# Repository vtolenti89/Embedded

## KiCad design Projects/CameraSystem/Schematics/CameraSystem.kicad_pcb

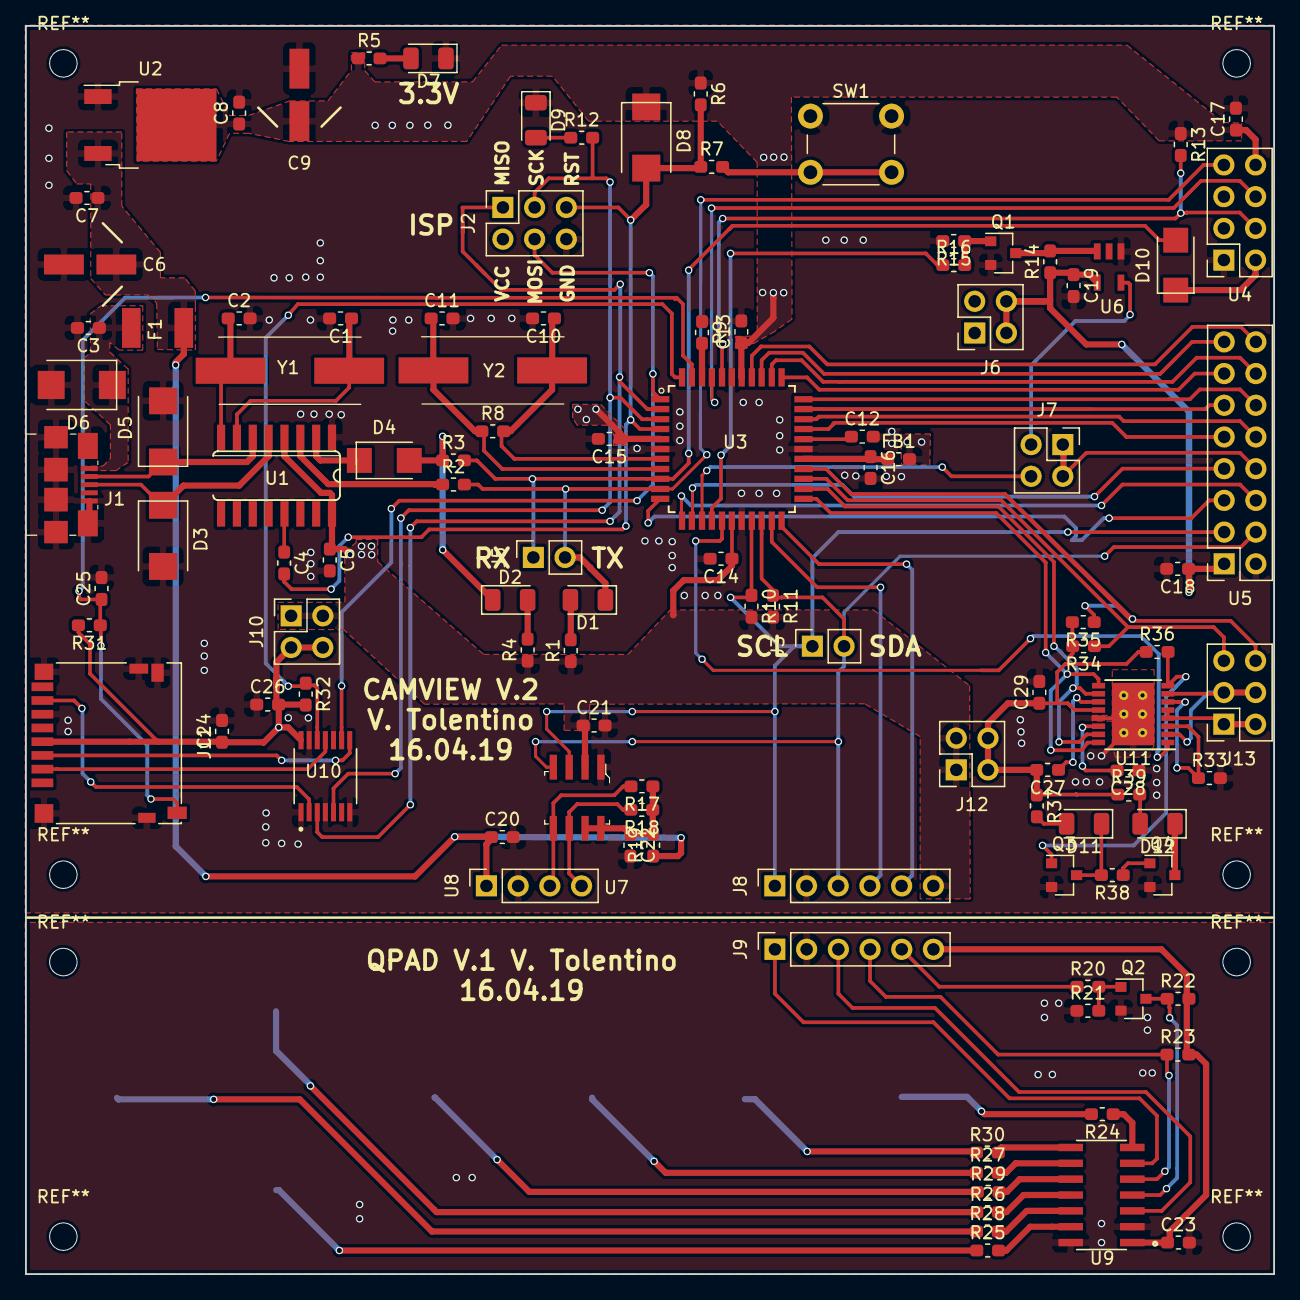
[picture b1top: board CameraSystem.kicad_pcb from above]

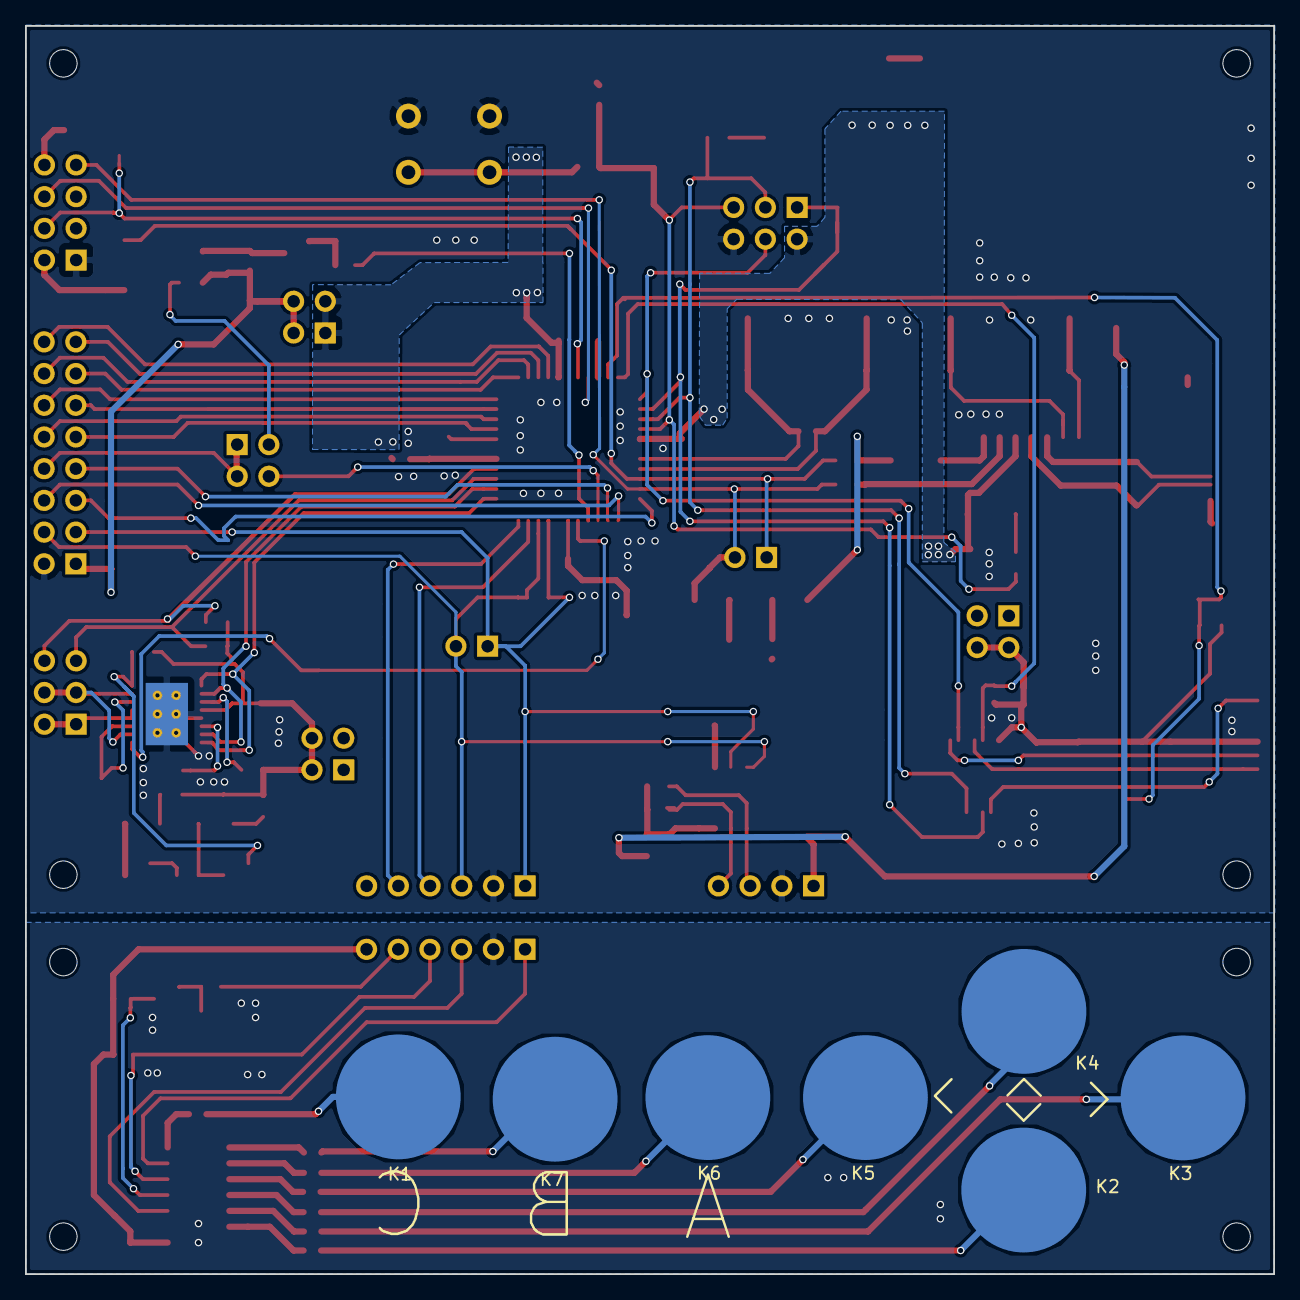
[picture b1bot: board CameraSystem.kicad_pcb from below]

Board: 2 copper layers, 100.0 x 100.0 mm, 119 parts (7 on the bottom side), 101 nets.

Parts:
C1, C2, C10, C11: 27p; C_0603_1608Metric_Pad1.05x0.95mm_HandSolder
C3, C4, C5, C12, C13, C14, C15, C16, C17, C18, C19, C20, C21, C22, C23, C24, C25, C26: 100n; C_0603_1608Metric_Pad1.05x0.95mm_HandSolder
C6, C9: EEE1VA470WP; PANASONIC_AL_SMD_D_D8
C7, C8: 1u; C_0603_1608Metric_Pad1.05x0.95mm_HandSolder
C27: 10n; C_0603_1608Metric_Pad1.05x0.95mm_HandSolder
C28: 2u2; C_0603_1608Metric_Pad1.05x0.95mm_HandSolder
C29: 10u; C_0603_1608Metric_Pad1.05x0.95mm_HandSolder
D1: BLUE_LED; LED_1206_3216Metric
D2: YELLOW_LED; LED_1206_3216Metric
D3, D5, D6, D8: SMBJ5.0CA; SMB_DO-214AA
D4, D10: SS14; SMA_DO-214AC
D7, D11: GREEN_LED; LED_1206_3216Metric
D9: LED; LED_1206_3216Metric
D12: RED_LED; LED_1206_3216Metric
F1: MF-MSMF075/24; PTC_MF-MSMF
FB1: BLM18PG121SN1D; R_0603_1608Metric_Pad1.05x0.95mm_HandSolder
J1: 10118192-0001LF; USB_Micro_B_Female_10118192
J2, J13: Conn_02x03_Odd_Even; PinSocket_2x03_P2.54mm_Vertical
J3, J5: Conn_01x02; PinSocket_1x02_P2.54mm_Vertical
J6, J7, J10, J12: Conn_02x02_Odd_Even; PinSocket_2x02_P2.54mm_Vertical
J8, J9: Conn_01x06; PinSocket_1x06_P2.54mm_Vertical
J11: DM3D-SF; microSD_HC_Hirose_DM3D-SF
K1, K2, K3, K4, K5, K6, K7: TouchPad; QPad_Round_D10
Q1, Q2, Q3, Q4: BC847; SOT-23
R1, R4, R5, R12, R37, R39: 560; R_0603_1608Metric_Pad1.05x0.95mm_HandSolder
R2, R3: 1k; R_0603_1608Metric_Pad1.05x0.95mm_HandSolder
R6, R9, R13, R14, R15, R31, R32, R34, R35: 10k; R_0603_1608Metric_Pad1.05x0.95mm_HandSolder
R7: 330; R_0603_1608Metric_Pad1.05x0.95mm_HandSolder
R8: 1M; R_0603_1608Metric_Pad1.05x0.95mm_HandSolder
R10, R11: 2K2; R_0603_1608Metric_Pad1.05x0.95mm_HandSolder
R16: 4k7; R_0603_1608Metric_Pad1.05x0.95mm_HandSolder
R17, R18: 1K74; R_0603_1608Metric_Pad1.05x0.95mm_HandSolder
R19: 200k; R_0603_1608Metric_Pad1.05x0.95mm_HandSolder
R20, R24, R25, R26, R27, R28, R29, R30: 4K7; R_0603_1608Metric_Pad1.05x0.95mm_HandSolder
R21, R22, R23: 10K; R_0603_1608Metric_Pad1.05x0.95mm_HandSolder
R33: 1; R_0603_1608Metric_Pad1.05x0.95mm_HandSolder
R36, R38: 47k; R_0603_1608Metric_Pad1.05x0.95mm_HandSolder
SW1: SW_Push; SW_PUSH_6mm_H4.3mm
U1: CH340; SO16
U2: AZ1117CD-3.3TRG1DICT-ND; TO-252-2
U3: ATMEGA16A-AU; QFP80P1200X1200X120-44N
U4: ESP8266; PinSocket_2x04_P2.54mm_Vertical
U5: OV7670; PinSocket_2x08_P2.54mm_Vertical
U6: SIT2001BI-S2-33E-24.000000G; SiT2001B_SOT23
U7: PCA9306D_118; SOIC-8_W3.9mm
U8: LCD_2x16_w_i2c; PinSocket_1x04_P2.54mm_Vertical
U9: AT42QT1070-SSUR
U10: MC74HC125ADTR2G; MC74HC125A_TSSOP−14
U11: DRV8833PWP; HTSSOP-16-1EP_4.4x5mm_P0.65mm_EP3.4x5mm_Mask2.46x2.31mm_The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
Y1: ABLS-12.000MHZ-B2-T; ABLS2-10.000MHZ-D4Y-T
Y2: ABLS2-10.000MHZ-D4Y-T

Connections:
/Camera/CAM_CLK: J7.4, U3.14
/Camera/CAM_D0: U3.37, U5.16
/Camera/CAM_D1: U3.36, U5.15
/Camera/CAM_D2: U3.35, U5.14
/Camera/CAM_D3: U3.34, U5.13
/Camera/CAM_D4: U3.33, U5.12
/Camera/CAM_D5: U3.32, U5.11
/Camera/CAM_D6: U3.31, U5.10
/Camera/CAM_D7: U3.30, U5.9
/Camera/CAM_HSYNC: U3.12, U5.6
/Camera/CAM_PCLK: U3.13, U5.7
/Camera/CAM_VSYNC: U3.11, U5.5
/Camera/CAM_XCLK_CTL: R16.1, U3.15
/Camera/SCL_3V3: J3.1, J8.1, R10.1, U3.19, U5.3, U7.3
/Camera/SDA_3V3: J3.2, J8.3, R11.1, U3.20, U5.4, U7.4
/Camera/VDD_3V3: C5.1, C8.1, C9.1, C13.1, C14.1, C15.1, C17.1, C21.1, D8.1, FB1.2, J2.2, J6.1, J6.3, J8.6, J10.1, J10.3, J12.1, J12.3, R1.1, R4.1, R5.1, R6.1, R10.2, R11.2, R13.1, U1.4, U1.16, U2.2, U3.5, U3.17, U3.38, U4.8, U7.2
/Camera/VDD_3V3_IN: C18.1, C19.1, J6.2, J6.4, R14.1, U5.1, U6.4
/Display/SCL_5V0: R18.2, U7.6, U8.4
/Display/SDA_5V0: R17.2, U7.5, U8.3
/Display/VDD_5V0: C6.1, C7.1, C20.1, F1.1, R19.1, U2.3, U8.1
/Input_Interface/USB_DN: D5.1, J1.2, U1.6
/Input_Interface/USB_DP: D3.1, J1.3, U1.5
/Input_Interface/USB_VCC: C3.1, D6.1, F1.2, J1.1
/Keypad/QP_GND: C23.2, J9.2, Q2.2, R21.1, U9.2, U9.14
/Keypad/QT_CHN: J9.4, R23.1, U9.5
/Keypad/QT_RST: J9.5, R20.1
/Keypad/SCL_3V3: J9.1, U9.6
/Keypad/SDA_3V3: J9.3, U9.3
/Keypad/VDD_3V3: C23.1, J9.6, R22.2, R23.2, U9.1
/Keypad/_QT_RST_IN: Q2.3, R22.1, U9.4
/Memory/SD_CS_IN: J11.2, U10.11
/Memory/SD_DATA_IN: J11.3, U10.8
/Memory/SD_DATA_OUT: J11.7, U10.2
/Memory/VDD_3V3_IN: C24.1, C26.2, J10.2, J10.4, J11.4, R31.2, R32.2, U10.14
/Memory/_SD_DET: C25.1, J11.10, R31.1, U3.43
/Microcontroller/CS: R32.1, U3.44, U10.12
/Microcontroller/MISO: J2.1, U3.2, U10.3
/Microcontroller/MOSI: J2.4, U3.1, U10.9
/Microcontroller/M_NSLEEP: U3.16, U11.1
/Microcontroller/M_PWM_IN_1: U3.23, U11.9, U11.16
/Microcontroller/M_PWM_IN_2: U3.24, U11.10, U11.15
/Microcontroller/QT_CHN: J8.4, U3.21
/Microcontroller/QT_RST: J8.5, U3.22
/Microcontroller/SCK: J2.3, R12.2, U3.3, U10.5
/Microcontroller/SENSOR1: J13.5, R34.1, U3.25
/Microcontroller/SENSOR2: J13.6, R35.1, U3.26
/Microcontroller/U2_SPI_RST: C4.2, D8.2, J2.5, R6.2, R7.1, U3.4
/Microcontroller/UC_SPI_RX: D10.2, J5.1, R3.2, U3.9
/Microcontroller/UC_SPI_TX: D1.1, J5.2, R2.2, U3.10, U4.7
/Microcontroller/WIFI_EN: R13.2, U3.40, U4.4
/Microcontroller/WIFI_RST: U3.41, U4.6
/Motor/M_PWM_OUT_1: J13.3, J13.4, U11.2, U11.7
/Motor/M_PWM_OUT_2: J13.1, J13.2, U11.4, U11.5
/Motor/VDD_3V3_CON_IN: C27.2, C29.1, J12.2, J12.4, R34.2, R35.2, R36.1, R37.1, R39.1, U11.12
GND: C1.2, C2.2, C3.2, C5.2, C6.2, C7.2, C8.2, C9.2, C10.2, C11.2, C12.2, C13.2, C14.2, C15.2, C16.2, C17.2, C18.2, C19.2, C20.2, C21.2, C22.2, C24.2, C25.2, C26.1, C28.1, C29.2, D3.2, D5.2, D6.2, D7.1, D9.1, J1.5, J1.SH, J2.6, J8.2, J11.6, J11.9, J11.11, Q1.2, Q3.2, Q4.2, R9.1, R15.2, R33.2, SW1.1, U1.1, U2.1, U3.6, U3.18, U3.28, U3.39, U4.1, U5.2, U6.1, U7.1, U8.2, U10.1, U10.4, U10.7, U10.10, U10.13, U11.13, U11.17
unnamed: C1.1, U1.7, Y1.1
unnamed: C2.1, U1.8, Y1.2
unnamed: C4.1, U1.13
unnamed: C10.1, R8.2, U3.7, Y2.1
unnamed: C11.1, R8.1, U3.8, Y2.2
unnamed: C12.1, U3.29
unnamed: C16.1, FB1.1, U3.27
unnamed: C22.1, R17.1, R18.1, R19.2, U7.7, U7.8
unnamed: C27.1, U11.11
unnamed: C28.2, U11.14
unnamed: D1.2, R1.2
unnamed: D2.1, D4.2, R3.1
unnamed: D2.2, R4.2
unnamed: D4.1, U1.2
unnamed: D7.2, R5.2
unnamed: D9.2, R12.1
unnamed: D10.1, U4.2
unnamed: D11.1, Q3.3, R38.2
unnamed: D11.2, R37.2
unnamed: D12.1, Q4.3
unnamed: D12.2, R39.2
unnamed: J7.1, J7.3, U5.8
unnamed: J7.2, U6.5
unnamed: K1.1, R24.2
unnamed: K2.1, R25.1
unnamed: K3.1, R28.1
unnamed: K4.1, R26.1
unnamed: K5.1, R29.1
unnamed: K6.1, R27.1
unnamed: K7.1, R30.1
unnamed: Q1.1, R15.1, R16.2
unnamed: Q1.3, R14.2, U6.3
unnamed: Q2.1, R20.2, R21.2
unnamed: Q3.1, R36.2, U11.8
unnamed: Q4.1, R38.1
unnamed: R2.1, U1.3
unnamed: R7.2, SW1.2
unnamed: R9.2, U3.42
unnamed: R24.1, U9.7
unnamed: R25.2, U9.13
unnamed: R26.2, U9.11
unnamed: R27.2, U9.9
unnamed: R28.2, U9.12
unnamed: R29.2, U9.10
unnamed: R30.2, U9.8
unnamed: R33.1, U11.3, U11.6

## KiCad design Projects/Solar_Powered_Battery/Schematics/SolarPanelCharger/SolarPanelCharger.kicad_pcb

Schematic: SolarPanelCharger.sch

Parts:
C1, C2: 100n; C_0603_1608Metric_Pad1.05x0.95mm_HandSolder
D1, D2: SS14; SMA_DO-214AC
Q1, Q2: BC847; SOT-23
R1, R2: 51k; R_0603_1608Metric_Pad1.05x0.95mm_HandSolder
R3: 18k; R_0603_1608Metric_Pad1.05x0.95mm_HandSolder
R4, R9: 100k; R_0603_1608Metric_Pad1.05x0.95mm_HandSolder
R5, R8, R10: 10k; R_0603_1608Metric_Pad1.05x0.95mm_HandSolder
R6: 100; R_0603_1608Metric_Pad1.05x0.95mm_HandSolder
R7: 47k; R_0603_1608Metric_Pad1.05x0.95mm_HandSolder
U1: LM358; SOP-8_3.76x4.96mm_P1.27mm
U2: TL431DBZ; SOT-23

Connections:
/BOOST_5V0/BOOST_IN: D2.2; also elsewhere on the board
/Buck_5V0/BUCK_IN: D1.2, R1.1; also elsewhere on the board
/EN_BAT: Q2.3 (C), R10.2; also elsewhere on the board
/LOGIC_SUPPLY: C1.1, C2.1, D1.1, D2.1, R5.1, R8.1, R10.1, U1.8 (V+)
/VREF_3V0: R3.1, R5.2, U1.3 (+), U2.1
/_EN_BAT: Q1.3 (C), R8.2, R9.1; also elsewhere on the board
GND: C1.2, C2.2, Q1.2 (E), Q2.2 (E), R2.2, R4.2, R7.2, U1.4 (V-), U1.5 (+), U2.3; also elsewhere on the board
unnamed: Q1.1 (B), R6.1, R7.1
unnamed: Q2.1 (B), R9.2
unnamed: R1.2, R2.1, U1.2 (-)
unnamed: R3.2, R4.1, U2.2
unnamed: R6.2, U1.1
unnamed: U1.6 (-), U1.7

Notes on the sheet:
Solar Panel
Switch to battery if the input voltage is below 6V

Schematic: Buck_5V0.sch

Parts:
C3: 100u; CP_Radial_D5.0mm_P2.50mm
C4: 22u; C_0603_1608Metric_Pad1.05x0.95mm_HandSolder
C5: 6n8; C_0603_1608Metric_Pad1.05x0.95mm_HandSolder
D5: SS24; SMB_DO-214AA
L1: 15u; CD54
R11, R12: 3k3; R_0603_1608Metric_Pad1.05x0.95mm_HandSolder
R13: 5k1; R_0603_1608Metric_Pad1.05x0.95mm_HandSolder
R14: 10k; R_0603_1608Metric_Pad1.05x0.95mm_HandSolder
R15: 33k; R_0603_1608Metric_Pad1.05x0.95mm_HandSolder
U3: TD1583; SOP-8_3.76x4.96mm_P1.27mm

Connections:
/Buck_5V0/BUCK_5V0: C4.2, C5.2, L1.1, R13.1; also elsewhere on the board
/Buck_5V0/BUCK_IN: C3.1, R14.2, U3.2; also elsewhere on the board
/Buck_5V0/EN: R14.1, R15.1, U3.7
GND: C3.2, C4.1, D5.2, R11.2, R12.2, R15.2, U3.4; also elsewhere on the board
unnamed: C5.1, R11.1, R12.1, R13.2, U3.5
unnamed: D5.1, L1.2, U3.3

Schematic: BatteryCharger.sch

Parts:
C6, C7: 10u; C_0603_1608Metric_Pad1.05x0.95mm_HandSolder
D6: YELLOW; LED_1206_3216Metric_Pad1.42x1.75mm_HandSolder
D7: GREEN; LED_1206_3216Metric_Pad1.42x1.75mm_HandSolder
J2: Conn_01x05_Female; PinSocket_1x05_P2.54mm_Vertical
Q3: BC847; SOT-23
R16, R17: 1; R_0603_1608Metric_Pad1.05x0.95mm_HandSolder
R18: 33k; R_0603_1608Metric_Pad1.05x0.95mm_HandSolder
R19, R23: 10k; R_0603_1608Metric_Pad1.05x0.95mm_HandSolder
R20: 18k; R_0603_1608Metric_Pad1.05x0.95mm_HandSolder
R21: 4.7k; R_0603_1608Metric_Pad1.05x0.95mm_HandSolder
R22: 51k; R_0603_1608Metric_Pad1.05x0.95mm_HandSolder
R24, R25: 1k; R_0603_1608Metric_Pad1.05x0.95mm_HandSolder
U4: TP4056; SOP-8_3.76x4.96mm_P1.27mm

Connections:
/BOOST_5V0/BOOST_IN: C7.1, J2.1, J2.2, U4.5; also elsewhere on the board
/BatteryCharger/EN: Q3.3 (C), R23.2, U4.8
/BatteryCharger/VCC: C6.1, R16.1, R17.1, R20.2, R23.1, R24.1, R25.1, U4.4
/BatteryCharger/temp: J2.5, R18.1, R20.1, U4.1
/Buck_5V0/BUCK_5V0: R16.2, R17.2; also elsewhere on the board
/EN_BAT: R21.1; also elsewhere on the board
GND: C6.2, C7.2, J2.3, J2.4, Q3.2 (E), R18.2, R19.1, R22.2, U4.3; also elsewhere on the board
unnamed: D6.1, U4.7
unnamed: D6.2, R24.2
unnamed: D7.1, U4.6
unnamed: D7.2, R25.2
unnamed: Q3.1 (B), R21.2, R22.1
unnamed: R19.2, U4.2

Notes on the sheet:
charging with 130mA
connects temp to one of MF52AT's terminal and the other one to the battery ground R(40°C)=26.6k R(-30°C)=31.8k
temp <0.45*Vin = 2.25V -> battery too hot temp <0.8*Vin = 4V -> battery too cold The temperature should stay below 40°C Vth_low(40°C)= = 2.22V Vth_high(-30°C)= = 3.19V

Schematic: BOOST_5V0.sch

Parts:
C8, C9: 22u; C_0603_1608Metric_Pad1.05x0.95mm_HandSolder
D8: SS24; SMB_DO-214AA
L2: 15u; CD54
R26: 7k5; R_0603_1608Metric_Pad1.05x0.95mm_HandSolder
R27, R29: 1k; R_0603_1608Metric_Pad1.05x0.95mm_HandSolder
R28: 22; R_0603_1608Metric_Pad1.05x0.95mm_HandSolder
U5: MT3608; SOT-23-6

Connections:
/BOOST_5V0/BOOST_IN: C9.1, L2.2, U5.5; also elsewhere on the board
/BOOST_5V0/BOOST_OUT: C8.1, D8.1, R26.1; also elsewhere on the board
/EN_BAT: R29.1; also elsewhere on the board
GND: C8.2, C9.2, R28.2, U5.2; also elsewhere on the board
unnamed: D8.2, L2.1, U5.1
unnamed: R26.2, R27.1, U5.3
unnamed: R27.2, R28.1
unnamed: R29.2, U5.4

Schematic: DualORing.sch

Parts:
C10, C11: 1n; C_0603_1608Metric_Pad1.05x0.95mm_HandSolder
C12, C13, C14, C15: 10u; C_0603_1608Metric_Pad1.05x0.95mm_HandSolder
D9, D10: 7V5; LL34
D11: BLUE; LED_1206_3216Metric_Pad1.42x1.75mm_HandSolder
D12: WHITE; LED_1206_3216Metric_Pad1.42x1.75mm_HandSolder
J3: USB_B_Female; USB_B_Female_right_angle
Q4, Q5, Q8, Q9: AO3401A; SOT-23
Q6, Q7: AO3400; SOT-23
R30, R31: 100k; R_0603_1608Metric_Pad1.05x0.95mm_HandSolder
R32, R33: 10k; R_0603_1608Metric_Pad1.05x0.95mm_HandSolder
R34, R35: 1k; R_0603_1608Metric_Pad1.05x0.95mm_HandSolder

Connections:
/BOOST_5V0/BOOST_OUT: Q5.3; also elsewhere on the board
/Buck_5V0/BUCK_5V0: Q4.3; also elsewhere on the board
/EN_BAT: D10.1, Q7.1, R31.1; also elsewhere on the board
/_EN_BAT: Q6.1, R30.1; also elsewhere on the board
GND: C12.2, C13.2, C14.2, C15.2, D10.2, J3.4, J3.SHELL1, Q6.2, Q7.2, R30.2, R31.2; also elsewhere on the board
unnamed: C10.1, Q4.2, Q8.2, R32.1
unnamed: C10.2, D12.1, Q4.1, Q6.3, Q8.1, R32.2
unnamed: C11.1, Q5.2, Q9.2, R33.1
unnamed: C11.2, D11.1, Q5.1, Q7.3, Q9.1, R33.2
unnamed: C12.1, C13.1, C14.1, C15.1, J3.1, Q8.3, Q9.3, R34.1, R35.2
unnamed: D11.2, R35.1
unnamed: D12.2, R34.2

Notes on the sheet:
Rds_on=0.06 Ohm
N.A.

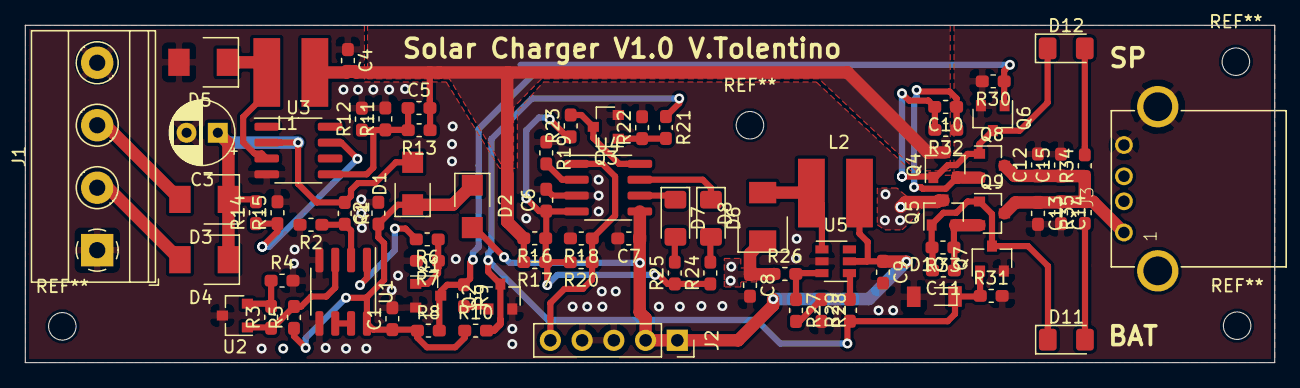
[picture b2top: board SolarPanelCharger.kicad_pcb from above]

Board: 2 copper layers, 100.0 x 27.0 mm, 80 parts (0 on the bottom side), 40 nets.

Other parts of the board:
D3, D4: SS24; SMB_DO-214AA
J1: Conn_01x04_Female; TerminalBlock_Phoenix_MKDS-1,5-4_1x04_P5.00mm_Horizontal

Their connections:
/Buck_5V0/BUCK_IN: D3.1, D4.1; also elsewhere on the board
GND: J1.1, J1.4; also elsewhere on the board
unnamed: D3.2, J1.3
unnamed: D4.2, J1.2

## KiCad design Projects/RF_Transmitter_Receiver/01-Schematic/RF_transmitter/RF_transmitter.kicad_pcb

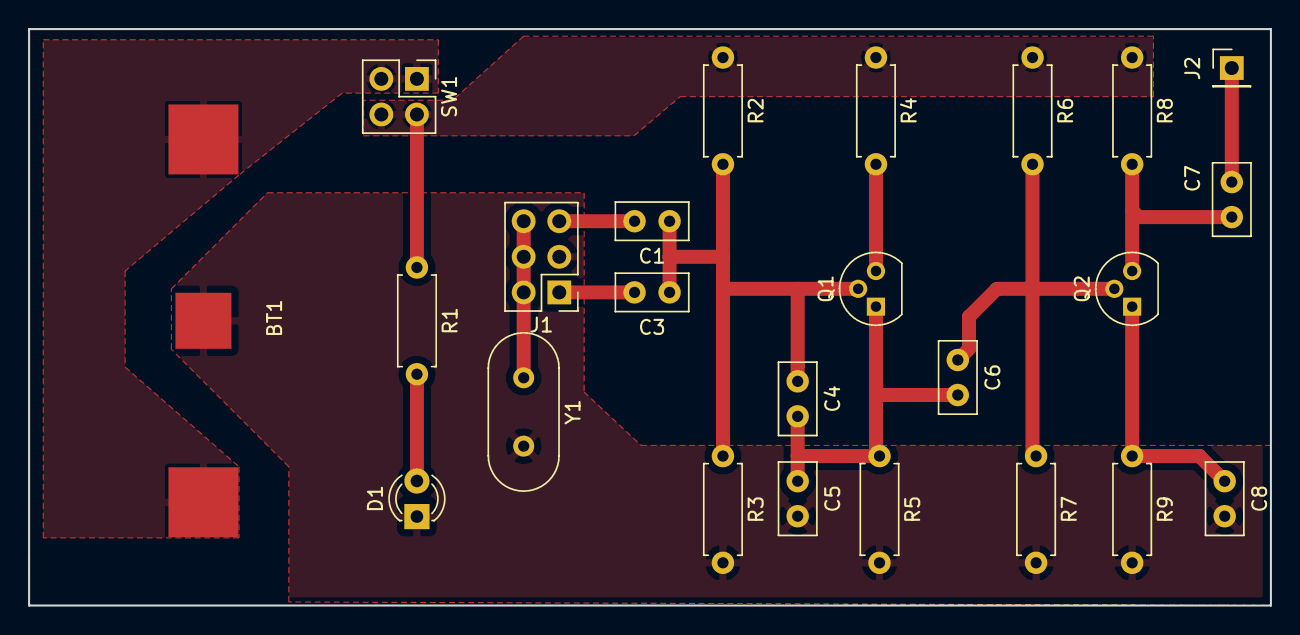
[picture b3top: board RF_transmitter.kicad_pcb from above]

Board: 2 copper layers, 88.6 x 41.1 mm, 24 parts (0 on the bottom side), 14 nets.

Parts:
BT1: Battery_Cell; BC2001-button-battery
C1: 22p; C_Disc_D5.0mm_W2.5mm_P2.50mm
C3: 50p; C_Disc_D5.0mm_W2.5mm_P2.50mm
C4, C5, C8: 470p; C_Disc_D5.0mm_W2.5mm_P2.50mm
C6, C7: 1n; C_Disc_D5.0mm_W2.5mm_P2.50mm
D1: LED; LED_D3.0mm
J1: Conn_02x03_Odd_Even; PinHeader_2x03_P2.54mm_Vertical
J2: Conn_01x01_Male; PinHeader_1x01_P2.54mm_Vertical
Q1, Q2: 2N3904; TO-92
R1: 620; R_Axial_DIN0207_L6.3mm_D2.5mm_P7.62mm_Horizontal
R2: 75k; R_Axial_DIN0207_L6.3mm_D2.5mm_P7.62mm_Horizontal
R3: 100k; R_Axial_DIN0207_L6.3mm_D2.5mm_P7.62mm_Horizontal
R4: 100; R_Axial_DIN0207_L6.3mm_D2.5mm_P7.62mm_Horizontal
R5: 2.2k; R_Axial_DIN0207_L6.3mm_D2.5mm_P7.62mm_Horizontal
R6: 22k; R_Axial_DIN0207_L6.3mm_D2.5mm_P7.62mm_Horizontal
R7: 10k; R_Axial_DIN0207_L6.3mm_D2.5mm_P7.62mm_Horizontal
R8: 1.5k; R_Axial_DIN0207_L6.3mm_D2.5mm_P7.62mm_Horizontal
R9: 240; R_Axial_DIN0207_L6.3mm_D2.5mm_P7.62mm_Horizontal
SW1: SW_Push_Dual; PinHeader_2x02_P2.54mm_Vertical
Y1: Crystal; Crystal_HC49-U_Vertical

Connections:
/VDD_3V0: BT1.1, SW1.1, SW1.3
/VDD_3V0_IN: R1.1, R2.1, R4.1, R6.1, R8.1, SW1.2, SW1.4
GND: BT1.2, C5.2, C8.2, D1.1, J1.3, R3.2, R5.2, R7.2, R9.2, Y1.2
unnamed: C1.1, C3.1, C4.1, Q1.2, R2.2, R3.1
unnamed: C1.2, J1.5
unnamed: C3.2, J1.1
unnamed: C4.2, C5.1, C6.2, Q1.1, R5.1
unnamed: C6.1, Q2.2, R6.2, R7.1
unnamed: C7.1, J2.1
unnamed: C7.2, Q2.3, R8.2
unnamed: C8.1, Q2.1, R9.1
unnamed: D1.2, R1.2
unnamed: J1.2, J1.4, J1.6, Y1.1
unnamed: Q1.3, R4.2

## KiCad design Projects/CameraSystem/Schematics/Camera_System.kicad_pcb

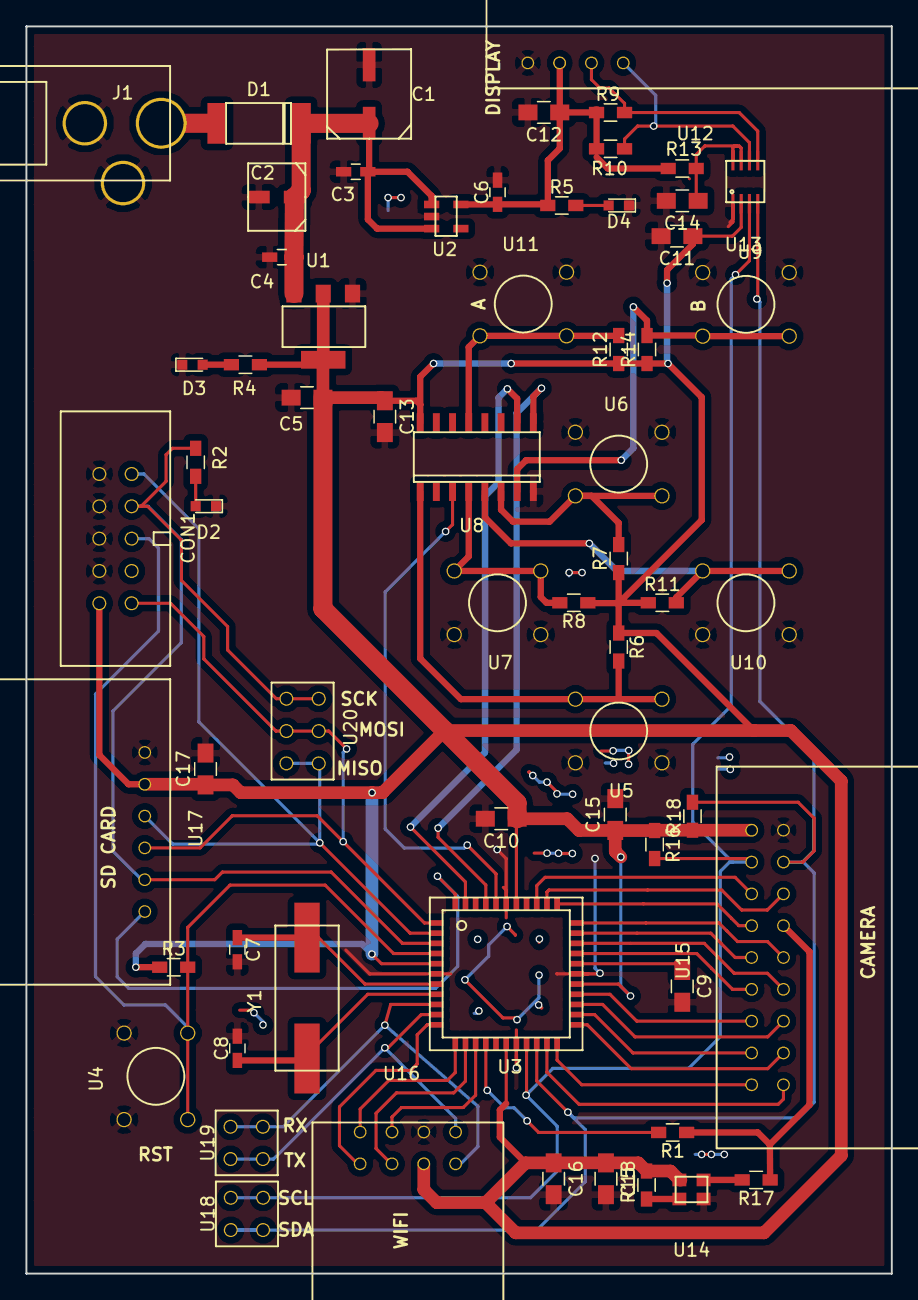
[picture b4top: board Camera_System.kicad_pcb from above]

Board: 2 copper layers, 68.0 x 98.0 mm, 63 parts (0 on the bottom side), 53 nets.

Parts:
C1: 47u; UWT1E470MCL6GS
C2: 10u; UWX1E100MCL1GB
C3: 1u; C_0603_HandSoldering
C4: 100n; C_0603_HandSoldering
C5: 22u; C_0805_HandSoldering
C6: 2.2u; C_0603_HandSoldering
C7, C8: 22p; C_0603_HandSoldering
C9, C10, C11, C12, C13, C14, C15, C16, C17, C18: 100n; C_0805_HandSoldering
CON1: AVR-ISP-10; N2510-6002RB
D1: CS3M
D2, D3, D4: LED; LED_0603
J1: BARREL_JACK; PJ-002B
R1: 0; R_0603_HandSoldering
R2, R4: 620; R_0603_HandSoldering
R3, R6, R7, R8, R11, R12, R14, R15: 10k; R_0603_HandSoldering
R5: 1k; R_0603_HandSoldering
R9, R10: 1.74k; R_0603_HandSoldering
R13: 200k; R_0603_HandSoldering
R16, R18: 4.7k; R_0603_HandSoldering
R17: 24.9; R_0603_HandSoldering
U1: IFX1117ME_V33
U2: LD2980ABM50TR
U3: ATMEGA16A-AU
U4, U5, U6, U7, U10, U11, U13: RT1105AF160Q
U8: CD4014B; CD4014B_SOIC
U9: PCA9306; PCA9306_SM8
U12: LCD_1602; LCD_header_2.5_4
U14: Si501; Si501_2x2.5
U15: OV7670-nofifo; Camera_ov7670_2.5_2x9
U16: ESP8266; wifi_header_female_2.5_2x4
U17: SDCARD; SDCARD_2.5_6
U18, U19: header_male_2.54_2x2
U20: header_male_2.54_2x3
Y1: Crystal; LFXTAL003210

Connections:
+3V3: C5.1, C10.1, C11.1, C13.1, C15.1, C16.1, C17.1, C18.1, CON1.2, R3.1, R4.1, R6.1, R7.1, R8.1, R11.1, R12.1, R14.1, R15.2, R16.1, R18.1, U1.2, U1.4, U3.5, U3.17, U3.27, U3.38, U8.16, U9.2, U14.4, U15.1, U16.7, U17.5
+5V: C6.1, C12.1, R5.1, R9.1, R10.1, R13.1, U2.5, U12.2
/3V3_SCL: R16.2, U3.19, U9.3, U15.3, U18.1, U18.2
/3V3_SDA: R18.2, U3.20, U9.4, U15.4, U18.3, U18.4
/5V_SCL: R10.2, U9.6, U12.4
/5V_SDA: R9.2, U9.5, U12.3
/CAM_D0: U3.23, U15.16
/CAM_D1: U3.24, U15.15
/CAM_D2: U3.25, U15.14
/CAM_D3: U3.26, U15.13
/CAM_D4: U3.31, U15.12
/CAM_D5: U3.30, U15.11
/CAM_D6: U3.33, U15.10
/CAM_D7: U3.32, U15.9
/CAM_HREF: U3.35, U15.6
/CAM_PCLK: U3.34, U15.7
/CAM_PWDN: U3.21, U15.18
/CAM_RST: U3.22, U15.17
/CAM_VSINC: U3.36, U15.5
/CAM_XCLK: R1.1, R17.1, U15.8
/CTRL_BTN1: R12.2, U8.13, U11.3, U11.4
/CTRL_BTN2: R14.2, U8.7, U13.3, U13.4
/CTRL_DOWN: R11.2, U8.5, U10.3, U10.4
/CTRL_LEFT: R6.2, U5.3, U5.4, U8.1
/CTRL_RIGHT: R7.2, U6.3, U6.4, U8.6
/CTRL_UP: R8.2, U7.3, U7.4, U8.4
/MIC_RST: CON1.5, R3.2, U3.4, U4.3, U4.4
/MISO: CON1.9, U3.2, U17.4, U20.1, U20.2
/MOSI: CON1.1, U3.1, U17.3, U20.3, U20.4
/P_S_CLK: U3.43, U8.10
/P_S_CTRL: U3.41, U8.9
/SCK: CON1.7, R2.1, U3.3, U17.2, U20.5, U20.6
/SDC_CS: U3.44, U17.1
/SERIAL_IN: U3.40, U8.3
/VDC_IN: C1.1, C2.1, C3.1, C4.1, D1.2, U1.3, U2.1, U2.3
/WLAN_CHPD: U3.14, U16.3
/WLAN_GPIO0: U3.13, U16.6
/WLAN_GPIO2: U3.12, U16.4
/WLAN_RST: U3.11, U16.5
/WLAN_RX: U3.9, U16.8, U19.1, U19.2
/WLAN_TX: U3.10, U16.1, U19.3, U19.4
GND: C1.2, C2.2, C3.2, C4.2, C5.2, C6.2, C7.2, C8.2, C9.2, C10.2, C11.2, C12.2, C13.2, C14.2, C15.2, C16.2, C17.2, C18.2, CON1.4, CON1.6, CON1.8, CON1.10, D2.1, D3.1, D4.1, J1.2, J1.3, U1.1, U2.2, U3.6, U3.18, U3.28, U3.39, U4.1, U4.2, U5.1, U5.2, U6.1, U6.2, U7.1, U7.2, U8.8, U9.1, U10.1, U10.2, U11.1, U11.2, U12.1, U13.1, U13.2, U14.2, U15.2, U16.2, U17.6
unnamed: C7.1, U3.7, Y1.1
unnamed: C8.1, U3.8, Y1.2
unnamed: C9.1, U3.29
unnamed: C14.1, R13.2, U9.7, U9.8
unnamed: D1.1, J1.1
unnamed: D2.2, R2.2
unnamed: D3.2, R4.2
unnamed: D4.2, R5.2
unnamed: R1.2, U3.15
unnamed: R15.1, U14.1
unnamed: R17.2, U14.3

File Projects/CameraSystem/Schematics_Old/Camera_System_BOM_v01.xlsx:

Source | C:/Users/vtolenti89/Documents/Projects/Kicad/Projects/Camera_System.sch
Kicad Rev | Eeschema 4.0.6
Generated Date | 42874.908217592594
Title | Not Set
Company | Not Set
Revision | Not Set
Date Issue | Not Set
Reference | Value | Voltage | Size | Part number | Library | Library Ref
J1 | BARREL_JACK |  |  | PJ-002B | conn | BARREL_JACK
C4 | 100n | 15 | 0603 | 06033C104K4T4A | device | C
C2 | 10u |  |  | UWX1E100MCL1GB | device | CP
C6 | 2.2u | 5 | 0603 | GRM188R61C225KE15J | device | C
C3 | 1u | 15 | 0603 | 885012106022 | device | C
C5 | 22u | 3.3 | 0805 | 0805ZD226KAT2A | device | C
U1 | IFX1117ME_V33 |  |  | IFX1117ME_V33 | MyLibrary | IFX1117ME_V33
U2 | LD2980ABM50TR |  |  | LD2980ABM50TR | MyLibrary | LD2980ABM50TR
D1 | CS3M |  |  | CS3M-E3/I | MyLibrary | CS3M
C1 | 47u |  |  | UWT1E470MCL6GS | device | CP
C10 | 100n | 3.3 | 0805 | 885012207072 | device | C
R4 | 620 |  | 0603 |  | device | R
D3 | LED |  | 0603 |  | device | LED
R5 | 1k |  | 0603 |  | device | R
D4 | LED |  | 0603 |  | device | LED
R1 | 0 |  | 0603 |  | device | R
Y1 | Crystal |  |  | LFXTAL003210Reel | device | Crystal
C7 | 22p | 3.3 | 0603 | VJ0603A220JXACW1BC | device | C
C8 | 22p | 3.3 | 0603 | VJ0603A220JXACW1BC | device | C
R3 | 10k |  | 0603 |  | device | R
U4 | RT1105AF160Q |  |  | RT1105AF160Q | MyLibrary | RT1105AF160Q
U16 | ESP8266 |  |  | 929975-01-07 | MyLibrary | ESP8266
U15 | OV7670-nofifo |  |  | 929975-01-07 | Camera_System-rescue | OV7670-nofifo-RESCUE-Camera_System
U17 | SDCARD |  |  | 90147-1106 | MyLibrary | SDCARD
CON1 | AVR-ISP-10 |  |  | N2510-5002RB | atmel | AVR-ISP-10
U3 | ATMEGA16A-AU |  |  | ATMEGA16A-AU | atmel | ATMEGA16A-AU
C16 | 100n | 3.3 | 0805 | 885012207072 | device | C
C15 | 100n | 3.3 | 0805 | 885012207072 | device | C
R2 | 620 |  | 0603 |  | device | R
D2 | LED |  | 0603 |  | device | LED
R16 | 4.7k |  | 0603 |  | device | R
R18 | 4.7k |  | 0603 |  | device | R
C17 | 100n | 3.3 | 0805 | 885012207072 | device | C
C9 | 100n | 3.3 | 0805 | 885012207072 | device | C
U14 | Si501 |  |  | 501JAA24M0000DAF | MyLibrary | Si501
R17 | 24.9 |  | 0603 |  | device | R
C18 | 100n | 3.3 | 0805 | 885012207072 | device | C
R15 | 10k |  | 0603 |  | device | R
U8 | CD4014B |  |  | CD4014BM96 | MyLibrary | CD4014B
C13 | 100n | 3.3 | 0805 | 885012207072 | device | C
R6 | 10k |  | 0603 |  | device | R
U5 | RT1105AF160Q |  |  | RT1105AF160Q | MyLibrary | RT1105AF160Q
R7 | 10k |  | 0603 |  | device | R
U6 | RT1105AF160Q |  |  | RT1105AF160Q | MyLibrary | RT1105AF160Q
R8 | 10k |  | 0603 |  | device | R
U7 | RT1105AF160Q |  |  | RT1105AF160Q | MyLibrary | RT1105AF160Q
R11 | 10k |  | 0603 |  | device | R
U10 | RT1105AF160Q |  |  | RT1105AF160Q | MyLibrary | RT1105AF160Q
R12 | 10k |  | 0603 |  | device | R
U11 | RT1105AF160Q |  |  | RT1105AF160Q | MyLibrary | RT1105AF160Q
R14 | 10k |  | 0603 |  | device | R
U13 | RT1105AF160Q |  |  | RT1105AF160Q | MyLibrary | RT1105AF160Q
U12 | LCD_1602 |  |  | 90147-1104 | MyLibrary | LCD_1602
C12 | 100n | 5 | 0805 | 885012207072 | device | C
U9 | PCA9306 |  |  | PCA9306DP1,125 | MyLibrary | PCA9306
C14 | 100n | 5 | 0805 | 885012207072 | device | C
C11 | 100n | 3.3 | 0805 | 885012207072 | device | C
R9 | 1.74k |  | 0603 |  | device | R
R10 | 1.74k |  | 0603 |  | device | R
R13 | 200k |  | 0603 |  | device | R
U18 | header_male_2.54_2x2 |  |  | 70287-1101 | MyLibrary | header_male_2.54_2x2
U19 | header_male_2.54_2x2 |  |  | 70287-1101 | MyLibrary | header_male_2.54_2x2
U20 | header_male_2.54_2x3 |  |  | 70287-1101 | MyLibrary | header_male_2.54_2x3

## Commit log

2017-05-10 First Comment
2017-05-10 New Project Created
2017-05-10 New Files added
2017-05-10 Project tree has been configured
2017-05-10 Component and footprint library created
2017-05-11 Power Management Layout Created
2017-05-14 New symbols habe been added
2017-05-16 Schematic for additional modules have been created
2017-05-16 New footprints have been created
2017-05-17 Schematic has been finished and layout started
2017-05-18 Layout has been updated
2017-05-19 Layout first draft finished
2017-05-19 Layout has been reviewed and there are no electric problems with it
2017-05-23 BOM has been updated and the items added to the mouser website
2017-06-13 Code added
2017-11-05 RC_Toy project has been created
2017-11-05 Transmitter schematic has been updated
2017-11-05 BOM was created
2018-09-17 Project restructured
2018-09-30 Files were restructured
2018-09-30 feat: modify sd card design
2018-10-03 feat: add new usb datasheet
2018-10-03 feat: add ch340g and digikey libraries
2018-10-03 feat: set up layout
2018-10-03 feat: add schottky diode datasheet
2018-10-04 feat: add a test comment
2018-10-04 feat: add datasheet of oscillator and update pinout table
2018-10-04 feat: update pinout table
2018-10-05 feat:add led datasheets and microcontroler
2018-10-06 feat: add i2c ic, add additional datasheets and simulations
2018-10-06 feat: first draft of uc schematic created
2018-10-07 feat: add keypad schematic
2018-10-07 feat: schematic updated
2018-10-09 feat: 3.3 regulator housing changed due to temperature
2018-10-09 feat: swap UART ports of wifi module
2018-10-09 feat: add debugging pins
2018-10-10 feat: DRC run
2018-10-11 feat: add interface to Q Pad
2018-10-12 feat: add new motor module to the schematic
2018-10-12 feat: add new datasheet for CH430G
2018-10-12 feat: add draft mechanical model
2018-10-12 feat: symbol assignment updated
2018-10-13 feat: assign footprints
2018-10-13 feat: updated custom symbols
2018-10-13 feat: start layout
2018-10-14 feat: position components in layout
2018-10-14 feat: update layout
2018-10-14 feat: layout updated
2018-10-16 feat: routing first draft finished
2018-10-17 feat: update gerber files
2018-10-18 FM_disturber: add new files
2018-10-19 FM_disturber:simulation updated
2018-10-22 FM_disturber: update coil inductance formula
2018-10-24 CameraSystem: BOM updated
2018-10-25 blog: added images
2018-10-25 blog: add new pictures
2018-10-26 blog: added pictures
2018-10-31 blog: update pictures
2018-11-07 RF_transmitter_receiver: add new schematic files
2019-01-28 Camera System software first draft
2019-01-28 change software to c++
2019-01-28 Camera System QT Pad schematic reviewed
2019-03-15 updated i2c code
2019-03-27 replace tvs diodes of camera system
2019-04-01 add inventory list
2019-04-01 update inventory list
2019-04-02 update inventory
2019-04-02 linux adaptation
2019-04-02 wifi module added
2019-04-03 circuit updated
2019-04-04 change circuit
2019-04-04 schematic updated
2019-04-04 update circuit
2019-04-07 camera was updated
2019-04-07 new solar panel project created
2019-04-08 block diagram updated
2019-04-09 SP specs updated
2019-04-09 update specs of solar panel
2019-04-10 add simulation model solar panel
2019-04-10 updated sollar cell
2019-04-11 add buck converter model
2019-04-12 add new solar panel schematic
2019-04-14 update solar panel schematic
2019-04-15 pcb updated
2019-04-15 camera layout updated
2019-04-16 generate merged layout
2019-04-17 create watering system project
2019-04-18 add gerber files for watering project
2019-05-06 add web app
2019-05-07 watering app updated
2019-05-07 update watering app
2019-05-12 structure web watering software
2019-05-13 update water web app
2019-05-13 nothing changed
2019-05-14 nothing hcanged
2019-05-15 watering app started to receive data
2019-05-19 update app
2019-05-21 code updated
2019-05-22 add water project
2019-05-22 wifi software working
2019-05-22 web app updated
2019-05-26 update bom
2019-06-13 add websocket
2019-07-04 make modifications to the solar charger circuit
2019-10-30 Bump eslint-utils
    Bumps [eslint-utils](https://github.com/mysticatea/eslint-utils) from 1.3.1 to 1.4.3.
    - [Release notes](https://github.com/mysticatea/eslint-utils/releases)
    - [Commits](https://github.com/mysticatea/eslint-utils/compare/v1.3.1...v1.4.3)
2020-03-14 Bump acorn in /Projects/Watering_System/water-monitor-app/frontend
    Bumps [acorn](https://github.com/acornjs/acorn) from 5.7.3 to 5.7.4.
    - [Release notes](https://github.com/acornjs/acorn/releases)
    - [Commits](https://github.com/acornjs/acorn/compare/5.7.3...5.7.4)
2020-04-16 Bump https-proxy-agent
    Bumps [https-proxy-agent](https://github.com/TooTallNate/node-https-proxy-agent) from 2.2.1 to 2.2.4.
    - [Release notes](https://github.com/TooTallNate/node-https-proxy-agent/releases)
    - [Commits](https://github.com/TooTallNate/node-https-proxy-agent/compare/2.2.1...2.2.4)
2020-06-06 Bump websocket-extensions
    Bumps [websocket-extensions](https://github.com/faye/websocket-extensions-node) from 0.1.3 to 0.1.4.
    - [Release notes](https://github.com/faye/websocket-extensions-node/releases)
    - [Changelog](https://github.com/faye/websocket-extensions-node/blob/master/CHANGELOG.md)
    - [Commits](https://github.com/faye/websocket-extensions-node/compare/0.1.3...0.1.4)
2020-07-17 Bump lodash in /Projects/Watering_System/water-monitor-app/frontend
    Bumps [lodash](https://github.com/lodash/lodash) from 4.17.11 to 4.17.19.
    - [Release notes](https://github.com/lodash/lodash/releases)
    - [Commits](https://github.com/lodash/lodash/compare/4.17.11...4.17.19)
2020-07-17 Bump lodash in /Projects/Watering_System/water-monitor-app/backend
    Bumps [lodash](https://github.com/lodash/lodash) from 4.17.11 to 4.17.19.
    - [Release notes](https://github.com/lodash/lodash/releases)
    - [Commits](https://github.com/lodash/lodash/compare/4.17.11...4.17.19)
2020-09-04 Bump handlebars in /Projects/Watering_System/water-monitor-app/frontend
    Bumps [handlebars](https://github.com/wycats/handlebars.js) from 4.1.2 to 4.7.6.
    - [Release notes](https://github.com/wycats/handlebars.js/releases)
    - [Changelog](https://github.com/handlebars-lang/handlebars.js/blob/master/release-notes.md)
    - [Commits](https://github.com/wycats/handlebars.js/compare/v4.1.2...v4.7.6)
2020-09-08 Bump http-proxy in /Projects/Watering_System/water-monitor-app/frontend
    Bumps [http-proxy](https://github.com/http-party/node-http-proxy) from 1.17.0 to 1.18.1.
    - [Release notes](https://github.com/http-party/node-http-proxy/releases)
    - [Changelog](https://github.com/http-party/node-http-proxy/blob/master/CHANGELOG.md)
    - [Commits](https://github.com/http-party/node-http-proxy/compare/1.17.0...1.18.1)
2021-01-21 Bump socket.io in /Projects/Watering_System/water-monitor-app/backend
    Bumps [socket.io](https://github.com/socketio/socket.io) from 2.2.0 to 2.4.0.
    - [Release notes](https://github.com/socketio/socket.io/releases)
    - [Changelog](https://github.com/socketio/socket.io/blob/2.4.0/CHANGELOG.md)
    - [Commits](https://github.com/socketio/socket.io/compare/2.2.0...2.4.0)
2021-03-09 Bump elliptic in /Projects/Watering_System/water-monitor-app/frontend
    Bumps [elliptic](https://github.com/indutny/elliptic) from 6.4.1 to 6.5.4.
    - [Release notes](https://github.com/indutny/elliptic/releases)
    - [Commits](https://github.com/indutny/elliptic/compare/v6.4.1...v6.5.4)
